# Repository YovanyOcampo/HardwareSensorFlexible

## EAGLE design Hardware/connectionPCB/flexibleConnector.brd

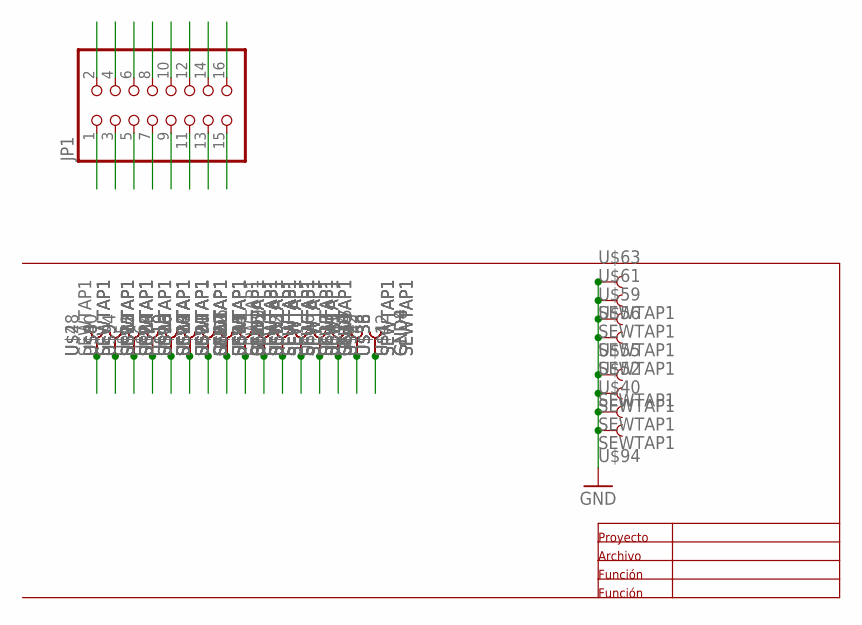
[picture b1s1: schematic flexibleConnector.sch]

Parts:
GND1, GND2, GND4, GND5, GND6, GND7, GND8, GND9: SEWTAP1; PETAL-LONG-1
JP1: PINHD-2X8; 2X08
U$1, U$2, U$3, U$4, U$5, U$6, U$7, U$8, U$9, U$10, U$11, U$12, U$13, U$14, U$15, U$16, U$17, U$18, U$19, U$20, U$21, U$22, U$23, U$24, U$25, U$26, U$27, U$28, U$29, U$30, U$31, U$32, U$33, U$34, U$35, U$36, U$38, U$40, U$41, U$42, U$43, U$44, U$48, U$49, U$50, U$52, U$53, U$54, U$55, U$56, U$58, U$59, U$60, U$61, U$63, U$65, U$85, U$88, U$89, U$90, U$91, U$92, U$93, U$94: SEWTAP1; PETAL-LONG-1

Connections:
1: GND4.1, GND8.1, JP1.1, U$22.1, U$43.1
2: JP1.2, U$1.1, U$41.1, U$42.1, U$49.1
3: JP1.3, U$35.1, U$36.1, U$38.1, U$58.1
4: GND5.1, GND7.1, JP1.4, U$18.1, U$34.1
5: JP1.5, U$17.1, U$32.1, U$33.1, U$53.1
6: GND2.1, GND9.1, JP1.6, U$16.1, U$65.1
7: JP1.7, U$15.1, U$31.1, U$44.1, U$93.1
8: GND1.1, GND6.1, JP1.8, U$50.1, U$92.1
9: JP1.9, U$21.1, U$29.1, U$30.1, U$91.1
10: JP1.10, U$14.1, U$27.1, U$28.1, U$88.1
11: JP1.11, U$13.1, U$25.1, U$26.1, U$90.1
12: JP1.12, U$20.1, U$23.1, U$24.1, U$89.1
13: JP1.13, U$7.1, U$11.1, U$12.1, U$85.1
14: JP1.14, U$9.1, U$10.1, U$19.1, U$54.1
15: JP1.15, U$4.1, U$6.1, U$8.1, U$60.1
16: JP1.16, U$2.1, U$3.1, U$5.1, U$48.1
GND: U$40.1, U$52.1, U$55.1, U$56.1, U$59.1, U$61.1, U$63.1, U$94.1

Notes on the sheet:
Proyecto
Archivo
Función

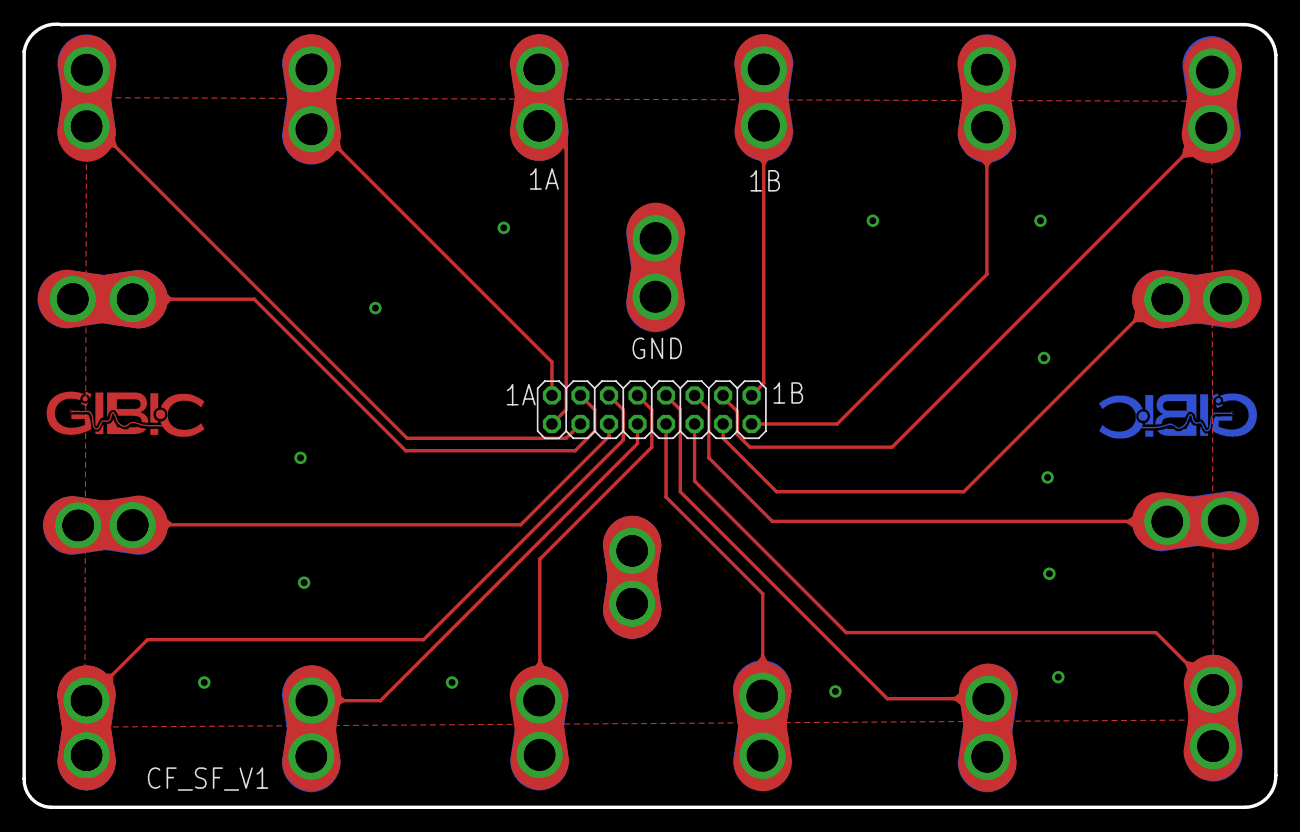
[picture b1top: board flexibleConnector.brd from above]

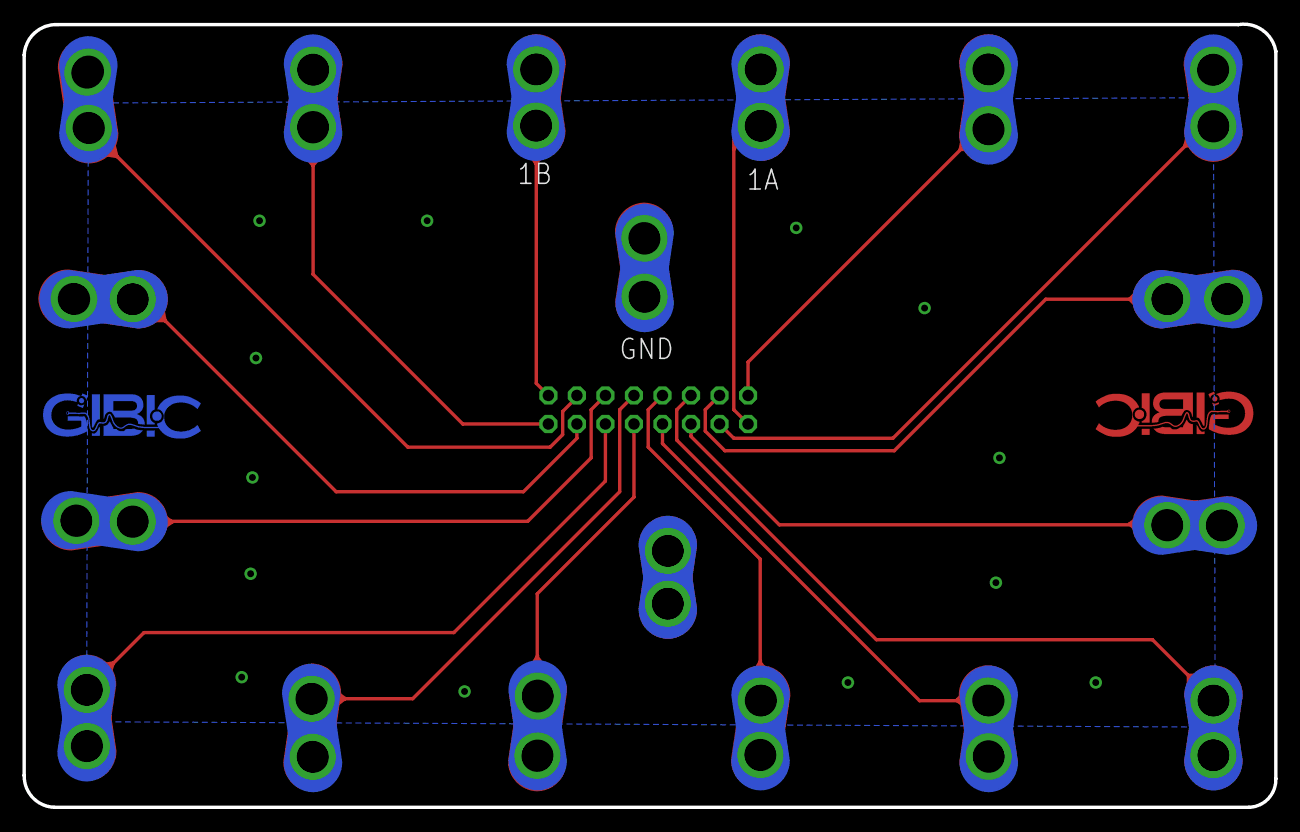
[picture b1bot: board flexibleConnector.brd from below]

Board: 2 copper layers, 111.4 x 69.7 mm, 73 parts (36 on the bottom side), 17 nets.

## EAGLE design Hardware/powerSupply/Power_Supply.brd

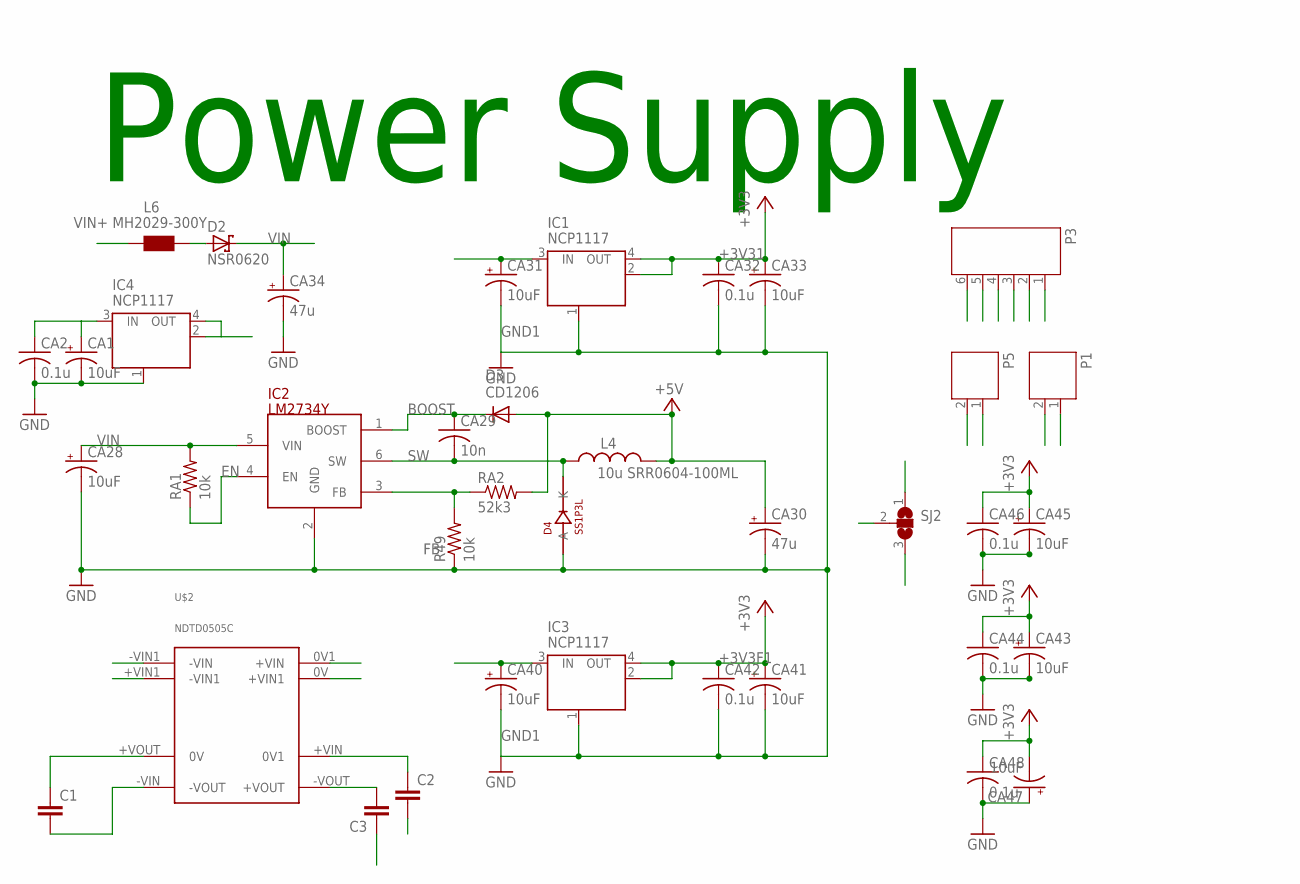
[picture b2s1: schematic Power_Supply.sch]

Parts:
C1, C2, C3: C-EUC1210; C1210
CA1, CA28, CA31, CA33, CA40, CA41, CA43, CA45, CA47: 10uF; B/3528-21W
CA2, CA32, CA42, CA44, CA46, CA48: 0.1u; C0805K@1
CA29: 10n; C0805
CA30, CA34: 47u; 140CLH-0810
D2: NSR0620; SMB
D3: CD1206; MINIMELF
D4: SS1P3L; DO220AAL
IC1, IC3, IC4: NCP1117; SOT223
IC2: LM2734Y; SOT23-6
L4: 10u SRR0604-100ML; SRR0604
L6: MH2029-300Y; 0805
P1, P5: JST-PH2
P3: JST-PH6
R49: 10k; R0805
RA1: 10k; R0805
RA2: 52k3; R0805
SJ2: SJ2W; SJ_2
U$2: NDTD0505C

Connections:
+3V3F1: CA41.+, CA42.1, IC3.2 (OUT), IC3.4 (OUT), P3.3
+3V31: CA32.1, CA33.+, IC1.2 (OUT), IC1.4 (OUT), P3.1
+5V: CA30.+, CA31.+, CA43.+, CA44.1, D3.A, IC1.3 (IN), L4.P$2 (2), P3.6, RA2.2, SJ2.1
+5V1: C1.1, CA40.+, CA45.+, CA46.1, IC3.3 (IN), U$2.+VOUT (0V)
+5V2: C2.1, SJ2.2, U$2.+VIN (0V1), U$2.+VIN1 (-VIN1)
+5V3: IC4.2 (OUT), IC4.4 (OUT), SJ2.3
-5V: C3.2, CA47.-, CA48.1, P3.5, U$2.-VOUT (+VOUT)
BOOST: CA29.1, D3.C, IC2.1 (BOOST)
EN: IC2.4 (EN), RA1.1
FB: IC2.3 (FB), R49.2, RA2.1
GND1: C1.2, C2.2, C3.1, CA1.-, CA2.2, CA28.-, CA30.-, CA31.-, CA32.2, CA33.-, CA34.-, CA40.-, CA41.-, CA42.2, CA43.-, CA44.2, CA45.-, CA46.2, CA47.+, CA48.2, D4.P$2 (A), IC1.1 (GND/ADJ), IC2.2 (GND), IC3.1 (GND/ADJ), IC4.1 (GND/ADJ), P1.1, P3.2, P3.4, R49.1, U$2.0V (+VIN1), U$2.0V1 (+VIN), U$2.-VIN (-VOUT), U$2.-VIN1 (-VIN)
unnamed: D2.A, L6.1
SW: CA29.2, D4.P$1 (K), IC2.6 (SW), L4.P$1 (1)
VIN: CA1.+, CA2.1, CA28.+, CA34.+, D2.C, IC2.5 (VIN), IC4.3 (IN), RA1.2
VIN2+: P1.2, P5.1
VIN+: L6.2, P5.2

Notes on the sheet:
Power Supply

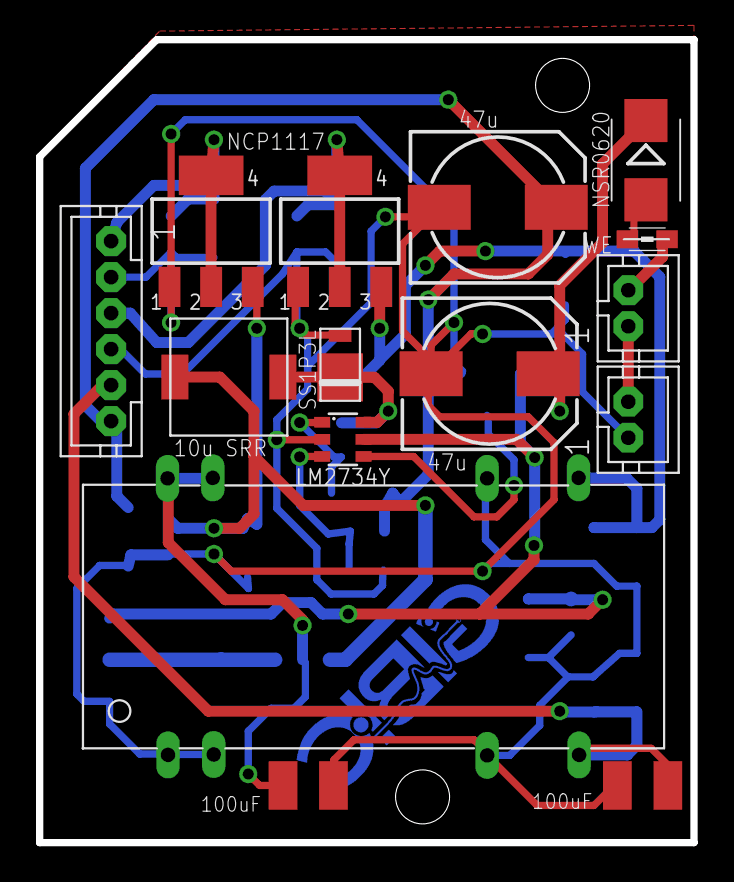
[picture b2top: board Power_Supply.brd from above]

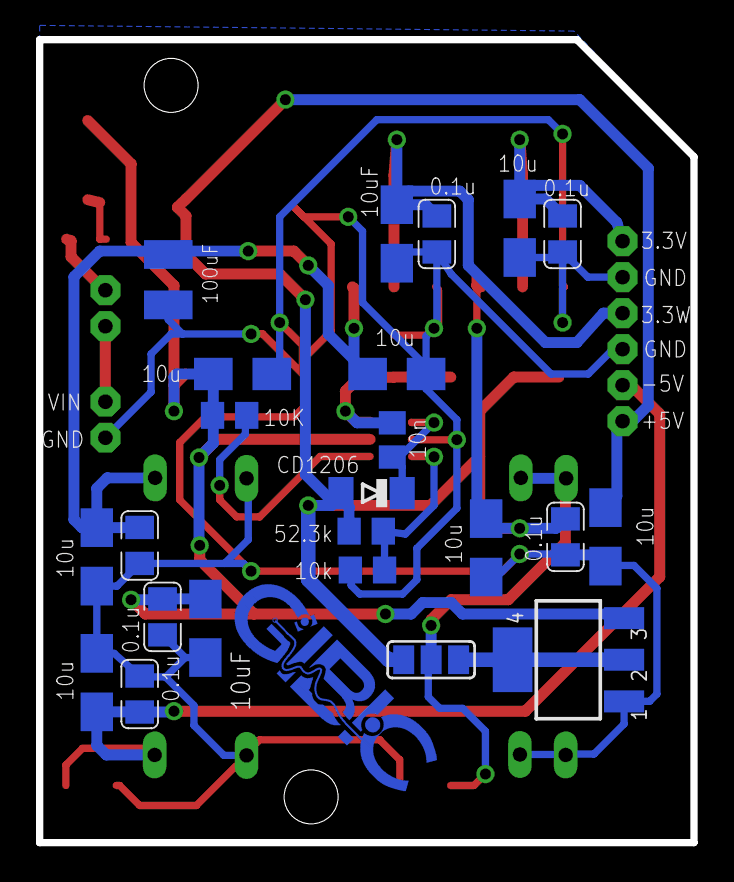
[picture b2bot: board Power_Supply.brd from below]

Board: 2 copper layers, 36.4 x 44.6 mm, 38 parts (23 on the bottom side), 16 nets.

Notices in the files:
parts and their libraries:
SparkFun-Aesthetics: Licensing: Creative Commons ShareAlike 4.0 International - https://creativecommons.org/licenses/by-sa/4.0
